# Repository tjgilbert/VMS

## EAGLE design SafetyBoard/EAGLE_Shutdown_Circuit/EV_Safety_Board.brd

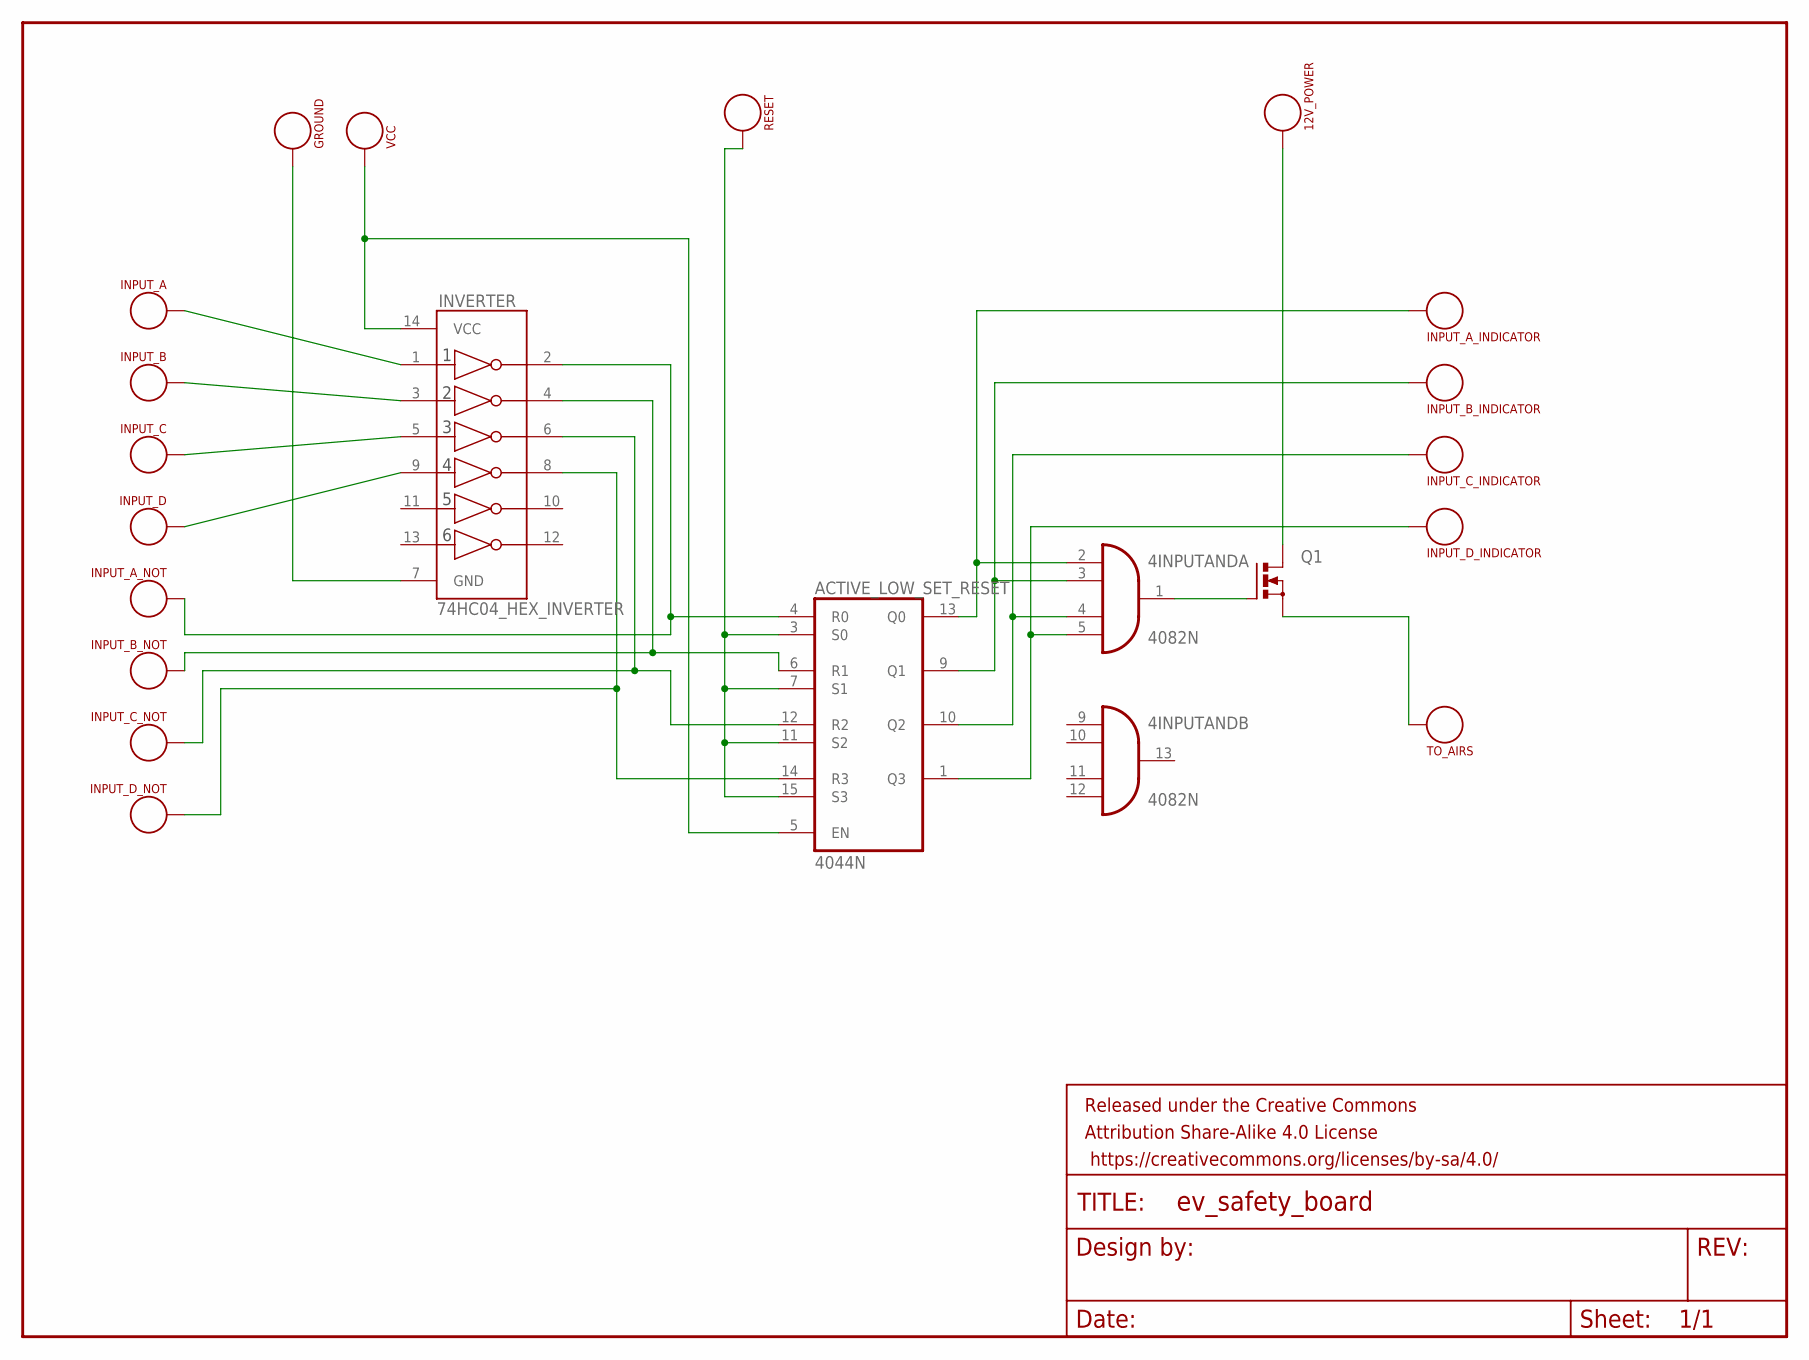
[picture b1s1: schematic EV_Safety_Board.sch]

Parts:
4INPUTAND: 4082N; DIL14
12V_POWER: SEW_HOLE; SIMPLE_HOLE
ACTIVE_LOW_SET_RESET: 4044N; DIL16
FRAME1: FRAME-LETTERNO_PACKAGE; DUMMY
GROUND: SEW_HOLE; SIMPLE_HOLE
INPUT_A: SEW_HOLE; SIMPLE_HOLE
INPUT_A_INDICATOR: SEW_HOLE; SIMPLE_HOLE
INPUT_A_NOT: SEW_HOLE; SIMPLE_HOLE
INPUT_B: SEW_HOLE; SIMPLE_HOLE
INPUT_B_INDICATOR: SEW_HOLE; SIMPLE_HOLE
INPUT_B_NOT: SEW_HOLE; SIMPLE_HOLE
INPUT_C: SEW_HOLE; SIMPLE_HOLE
INPUT_C_INDICATOR: SEW_HOLE; SIMPLE_HOLE
INPUT_C_NOT: SEW_HOLE; SIMPLE_HOLE
INPUT_D: SEW_HOLE; SIMPLE_HOLE
INPUT_D_INDICATOR: SEW_HOLE; SIMPLE_HOLE
INPUT_D_NOT: SEW_HOLE; SIMPLE_HOLE
INVERTER: 74HC04_HEX_INVERTER; DIL14
Q1: PMOSFET_NTO220BH; TO220BH
RESET: SEW_HOLE; SIMPLE_HOLE
TO_AIRS: SEW_HOLE; SIMPLE_HOLE
VCC: SEW_HOLE; SIMPLE_HOLE

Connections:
unnamed: 12V_POWER.P$1, Q1.D
unnamed: INPUT_A.P$1, INVERTER.1 (1A)
unnamed: INPUT_B.P$1, INVERTER.3 (2A)
unnamed: INPUT_C.P$1, INVERTER.5 (3A)
unnamed: INPUT_D.P$1, INVERTER.9 (4A)
unnamed: ACTIVE_LOW_SET_RESET.3 (S0), ACTIVE_LOW_SET_RESET.7 (S1), ACTIVE_LOW_SET_RESET.11 (S2), ACTIVE_LOW_SET_RESET.15 (S3), RESET.P$1
unnamed: ACTIVE_LOW_SET_RESET.6 (R1), INPUT_B_NOT.P$1, INVERTER.4 (2Y)
unnamed: ACTIVE_LOW_SET_RESET.12 (R2), INPUT_C_NOT.P$1, INVERTER.6 (3Y)
unnamed: ACTIVE_LOW_SET_RESET.14 (R3), INPUT_D_NOT.P$1, INVERTER.8 (4Y)
unnamed: 4INPUTAND.4 (I2), ACTIVE_LOW_SET_RESET.10 (Q2), INPUT_C_INDICATOR.P$1
unnamed: 4INPUTAND.3 (I1), ACTIVE_LOW_SET_RESET.9 (Q1), INPUT_B_INDICATOR.P$1
unnamed: 4INPUTAND.2 (I0), ACTIVE_LOW_SET_RESET.13 (Q0), INPUT_A_INDICATOR.P$1
unnamed: 4INPUTAND.1 (O), Q1.G
unnamed: Q1.S, TO_AIRS.P$1
unnamed: ACTIVE_LOW_SET_RESET.4 (R0), INPUT_A_NOT.P$1, INVERTER.2 (1Y)
unnamed: GROUND.P$1, INVERTER.7 (GND)
unnamed: 4INPUTAND.5 (I3), ACTIVE_LOW_SET_RESET.1 (Q3), INPUT_D_INDICATOR.P$1
unnamed: ACTIVE_LOW_SET_RESET.5 (EN), INVERTER.14 (VCC), VCC.P$1
VDD: 4INPUTAND.14 (VDD), ACTIVE_LOW_SET_RESET.16 (VDD)
VSS: 4INPUTAND.7 (VSS), ACTIVE_LOW_SET_RESET.8 (VSS)

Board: 2 copper layers, 22 parts (0 on the bottom side), 20 nets, no tracks yet.

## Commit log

2016-10-14 Created Solenoid Shifter project
2016-10-21 added safety board project folder

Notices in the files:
parts and their libraries:
LilyPad-Wearables: Licensing:Creative Commons ShareAlike 4.0 International - https://creativecommons.org/licenses/by-sa/4.0
SparkFun-Aesthetics: Released under the Creative Commons Attribution Share-Alike 4.0 License
SparkFun-Aesthetics: https://creativecommons.org/licenses/by-sa/4.0
